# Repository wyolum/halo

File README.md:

# halo
Desktop Edge-lit portrait stand.

[Instructions:](https://wyolum.com/how-to-edge-lit-portrait-work-in-progress/)

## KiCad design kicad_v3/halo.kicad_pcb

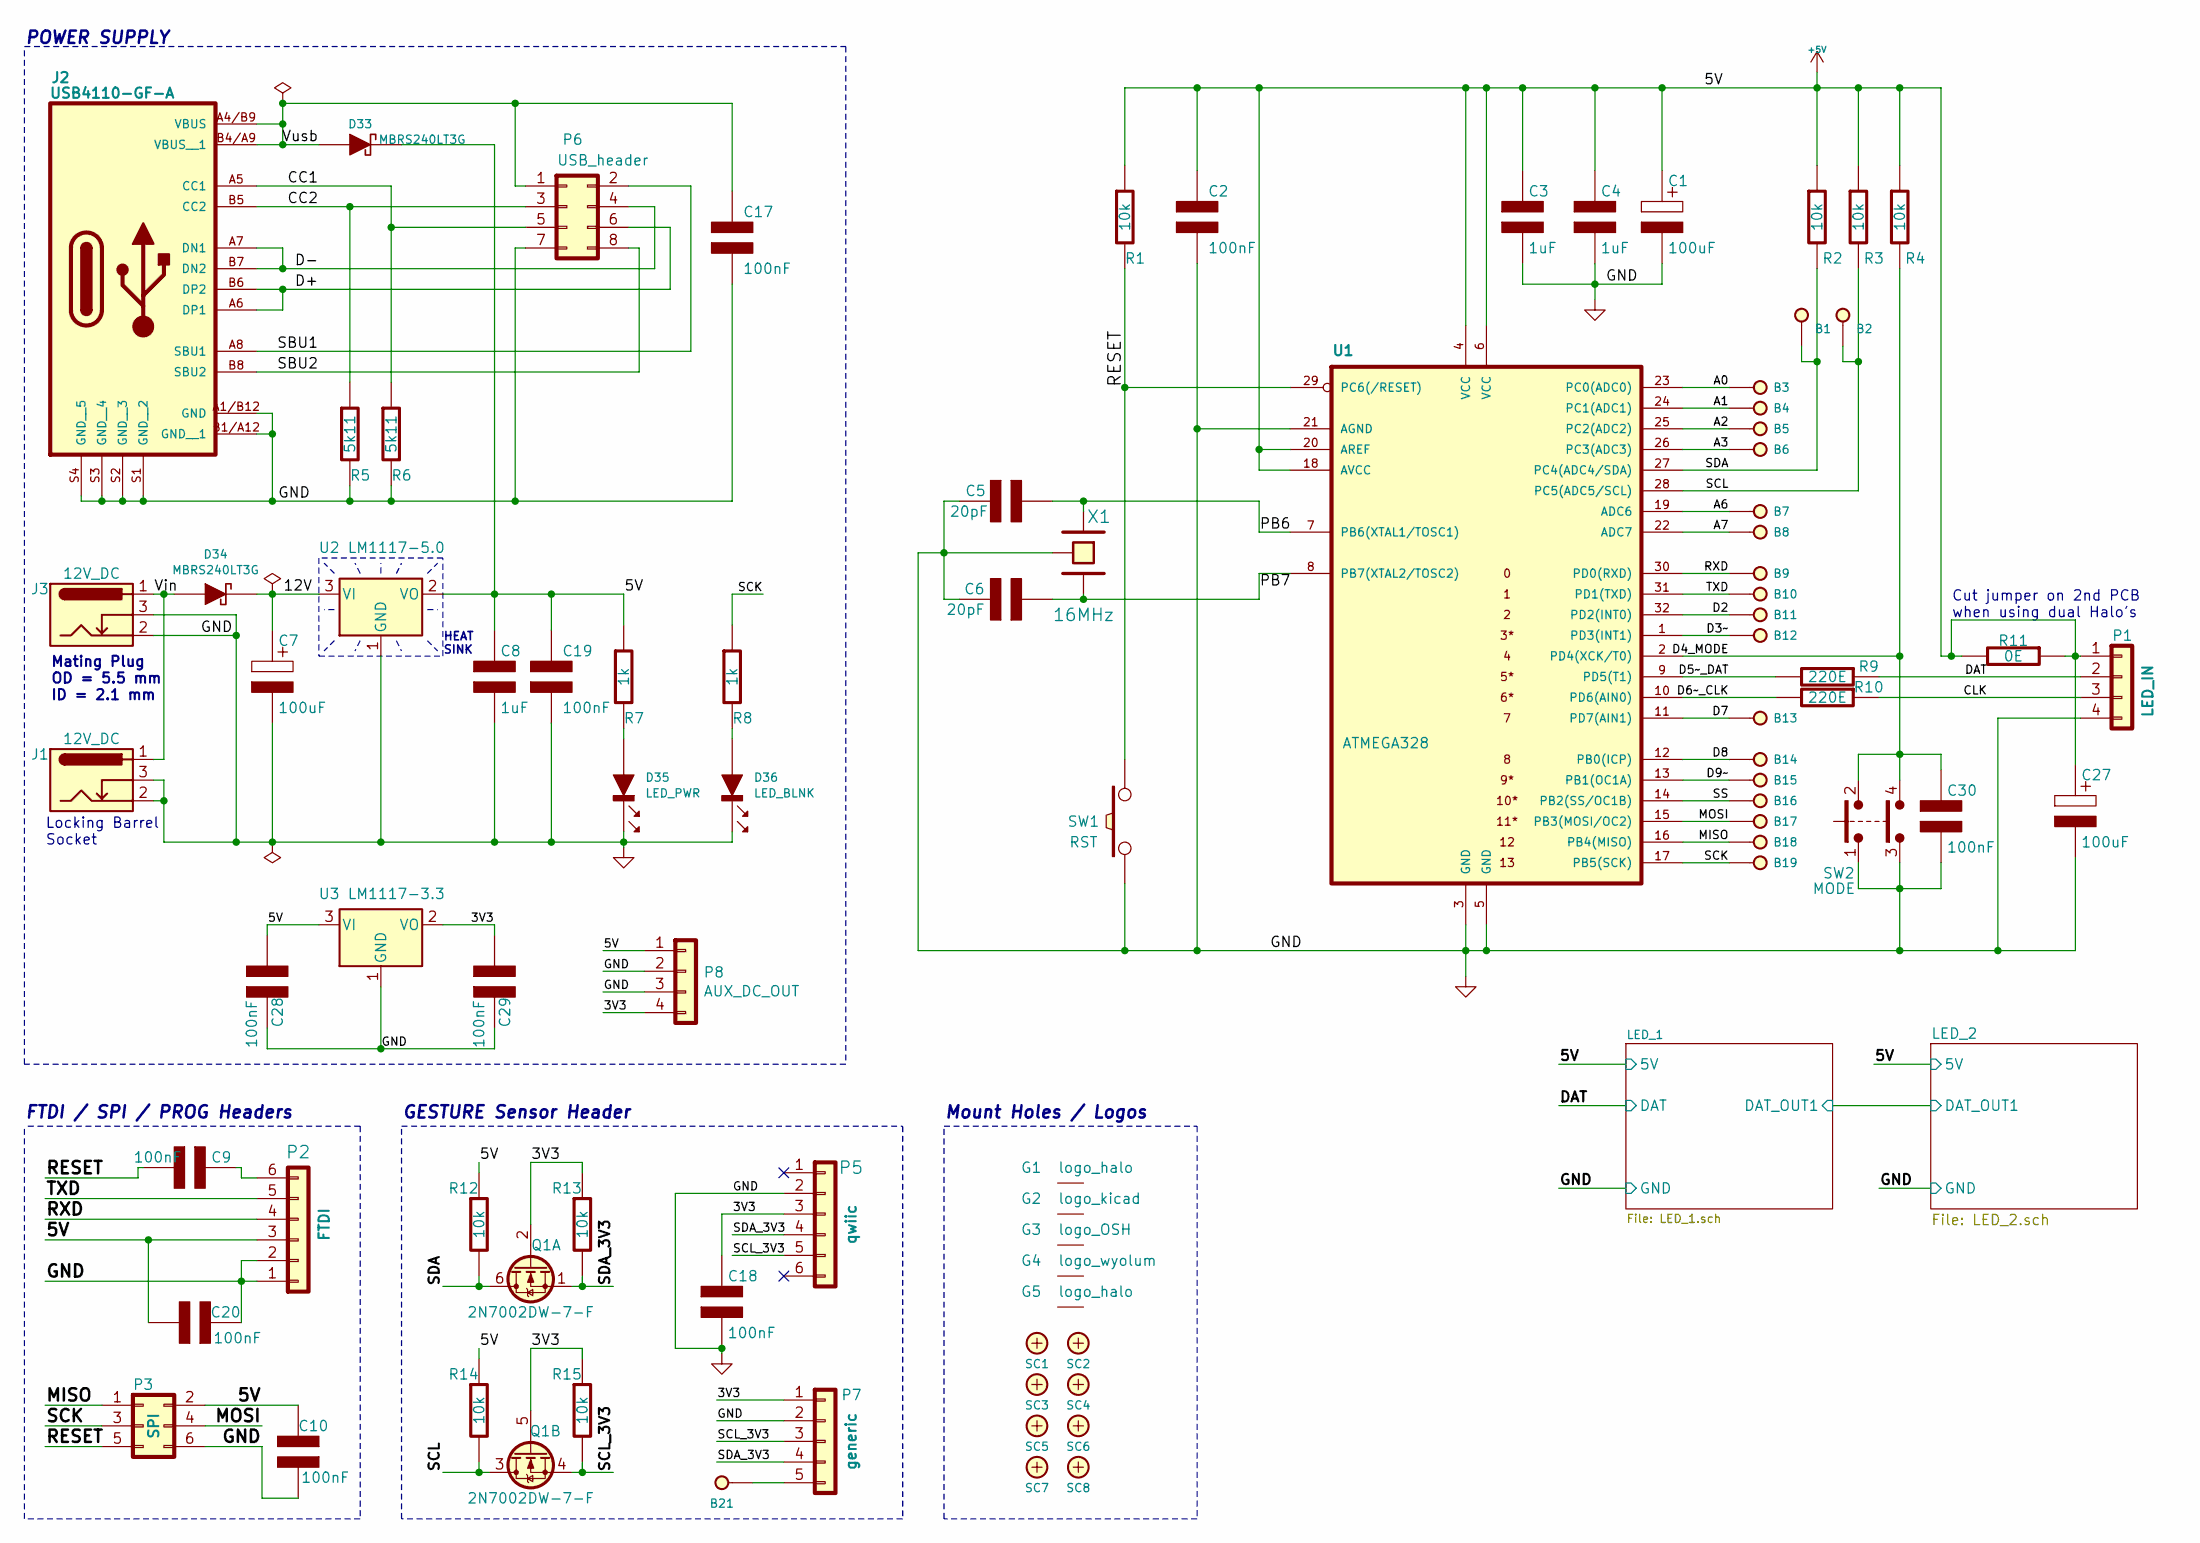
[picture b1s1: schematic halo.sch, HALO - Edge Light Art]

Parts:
B1, B2, B3, B4, B5, B6, B7, B8, B9, B10, B11, B12, B13, B14, B15, B16, B17, B18, B19, B21: I_O; breakout_smd
C1, C7, C27: 100uF; CP_Elec_6.3x7.7
C2, C9, C10, C17, C18, C19, C20, C28, C29, C30: 100nF; C_0805_2012Metric
C3, C4, C8: 1uF; C_0805_2012Metric
C5, C6: 20pF; C_0805_2012Metric; Digikey 490-1734-1-ND
D33, D34: MBRS240LT3G; D_SMB
D35: LED_PWR; LED_0805_2012Metric
D36: LED_BLNK; LED_0805_2012Metric
G1: logo_halo
G2: logo_kicad; logo_KiCad_12mm_SilkScreen
G3: logo_OSH; logo_OSHW_11.4x12mm_SilkScreen
G4: logo_wyolum
G5: logo_halo; logo_halo_10mm
J1: 12V_DC; conn_barrel
J2: USB4110-GF-A; GCT_USB4110-GF-A; PARTREV A
J3: 12V_DC; barrel_jack_DC-005-5A-2_5-SMT
P1: LED_IN; PinSocket_1x04_P2.54mm_Vertical_SMD_Pin1Left
P2: FTDI; PinHeader_1x06_P2.54mm_Vertical_SMD_Pin1Left
P3: SPI; TC2030-IDC
P5: qwiic; sparkfun_apds_9960_smd
P6: USB_header; PinHeader_2x04_P2.54mm_Vertical_SMD
P7: generic; generic_apds_9960_smd
P8: AUX_DC_OUT; PinSocket_1x04_P2.54mm_Vertical_SMD_Pin1Left
Q1: 2N7002DW-7-F; SOT-363_SC-70-6
R1, R2, R3, R4, R12, R13, R14, R15: 10k; R_0805_2012Metric
R5, R6: 5k11; R_0805_2012Metric
R7, R8: 1k; R_0805_2012Metric
R9, R10: 220E; R_0805_2012Metric
R11: 0E; R_0805_2012Metric
SC1, SC2, SC3, SC4, SC5, SC6, SC7, SC8: SCREW; MountingHole_3.2mm_M3_Pad_Via
SW1: RST; SW_Push_1P1T_NO_6x6mm_H9.5mm
SW2: MODE; PinHeader_2x02_P2.54mm_Vertical_SMD
U1: ATMEGA328; TQFP-32_7x7mm_P0.8mm
U2: LM1117-5.0; SOT-223-3_TabPin2
U3: LM1117-3.3; SOT-223-3_TabPin2
X1: 16MHz; Crystal_SMD_3225-4Pin_3.2x2.5mm

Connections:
+5V: C1.1, C2.1, C3.1, C4.1, C8.1, C10.2, C19.1, C20.1, C27.1, C28.1, D33.K, P1.1, P2.3, P3.2, P8.1, R1.1, R2.1, R3.1, R4.1, R7.1, R11.1, R11.2, R12.1, R14.1, U1.4 (VCC), U1.6 (VCC), U1.18 (AVCC), U1.20 (AREF), U2.2 (VO), U3.3 (VI); also elsewhere on the board
/3V3: C18.1, C29.1, P5.3, P7.1, P8.4, Q1.2 (G), Q1.5 (G), R13.1, R15.1, U3.2 (VO)
/12V: C7.1, D34.K, U2.3 (VI)
/A0: B3.1, U1.23 (PC0(ADC0))
/A1: B4.1, U1.24 (PC1(ADC1))
/A2: B5.1, U1.25 (PC2(ADC2))
/A3: B6.1, U1.26 (PC3(ADC3))
/A6: B7.1, U1.19 (ADC6)
/A7: B8.1, U1.22 (ADC7)
/CC1: J2.A5 (CC1), P6.5, R6.1
/CC2: J2.B5 (CC2), P6.3, R5.1
/CLK: P1.3, R10.1
/D2: B11.1, U1.32 (PD2(INT0))
/D3~~: B12.1, U1.1 (PD3(INT1))
/D4_MODE: C30.1, R4.2, SW2.2, SW2.4, U1.2 (PD4(XCK/T0))
/D5~~_DAT: R9.2, U1.9 (PD5(T1))
/D6~~_CLK: R10.2, U1.10 (PD6(AIN0))
/D7: B13.1, U1.11 (PD7(AIN1))
/D8: B14.1, U1.12 (PB0(ICP))
/D9~~: B15.1, U1.13 (PB1(OC1A))
/D+: J2.A6 (DP1), J2.B6 (DP2), P6.6
/D-: J2.A7 (DN1), J2.B7 (DN2), P6.4
/DAT: P1.2, R9.1; also elsewhere on the board
/MISO: B18.1, P3.1, U1.16 (PB4(MISO))
/MOSI: B17.1, P3.4, U1.15 (PB3(MOSI/OC2))
/PB6: C5.1, U1.7 (PB6(XTAL1/TOSC1)), X1.1
/PB7: C6.2, U1.8 (PB7(XTAL2/TOSC2)), X1.3
/RESET: C9.2, P3.5, R1.2, SW1.2, U1.29 (PC6(/RESET))
/RXD: B9.1, P2.4, U1.30 (PD0(RXD))
/SBU1: J2.A8 (SBU1), P6.2
/SBU2: J2.B8 (SBU2), P6.8
/SCK: B19.1, P3.3, R8.1, U1.17 (PB5(SCK))
/SCL: B2.1, Q1.3 (D), R3.2, R14.2, U1.28 (PC5(ADC5/SCL))
/SCL_3V3: P5.5, P7.3, Q1.4 (S), R15.2
/SDA: B1.1, Q1.6 (D), R2.2, R12.2, U1.27 (PC4(ADC4/SDA))
/SDA_3V3: P5.4, P7.4, Q1.1 (S), R13.2
/SS: B16.1, U1.14 (PB2(SS/OC1B))
/TXD: B10.1, P2.5, U1.31 (PD1(TXD))
/Vin: D34.A, J1.1, J3.1
/Vusb: C17.1, D33.A, J2.A4/B9 (VBUS), J2.B4/A9 (VBUS__1), P6.1
GND: C1.2, C2.2, C3.2, C4.2, C5.2, C6.1, C7.2, C8.2, C10.1, C17.2, C18.2, C19.2, C20.2, C27.2, C28.2, C29.2, C30.2, D35.K, D36.K, J1.2, J1.3, J2.A1/B12 (GND), J2.B1/A12 (GND__1), J2.S1 (GND__2), J2.S2 (GND__3), J2.S3 (GND__4), J2.S4 (GND__5), J3.2, J3.3, P1.4, P2.1, P2.2, P3.6, P5.2, P6.7, P7.2, P8.2, P8.3, R5.2, R6.2, SW1.1, SW2.1, SW2.3, U1.3 (GND), U1.5 (GND), U1.21 (AGND), U2.1 (GND), U3.1 (GND), X1.GND; also elsewhere on the board
unnamed: C9.1, P2.6
unnamed: D35.A, R7.2
unnamed: D36.A, R8.2

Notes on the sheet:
FTDI / SPI / PROG Headers
Mount Holes / Logos
HEAT SINK
Mating Plug OD = 5.5 mm ID = 2.1 mm
Cut jumper on 2nd PCB when using dual Halo's
Locking Barrel Socket
GESTURE Sensor Header
POWER SUPPLY

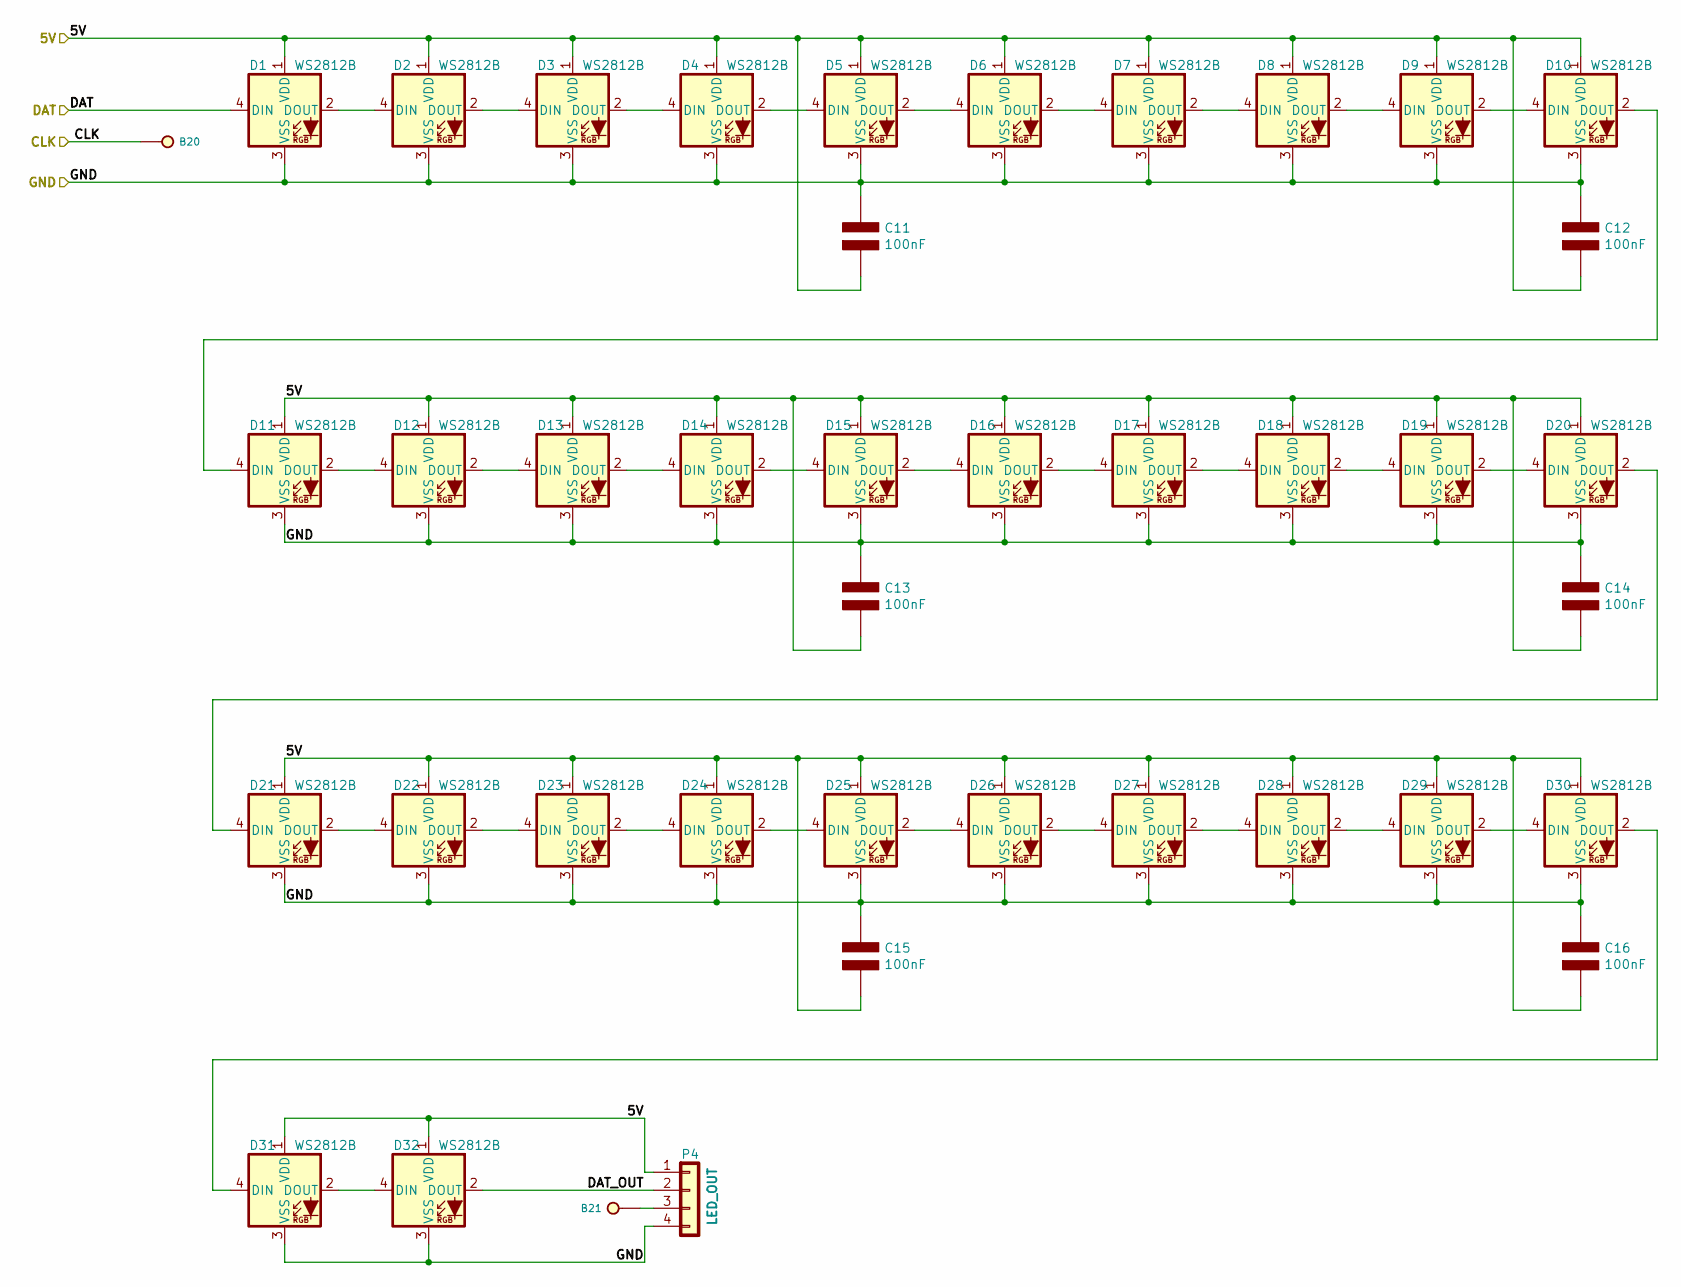
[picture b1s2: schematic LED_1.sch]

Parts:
B20, B21: I_O; breakout_smd
C11, C12, C13, C14, C15, C16: 100nF; C_0805_2012Metric
D1, D2, D3, D4, D5, D6, D7, D8, D9, D10, D11, D12, D13, D14, D15, D16, D17, D18, D19, D20, D21, D22, D23, D24, D25, D26, D27, D28, D29, D30, D31, D32: WS2812B; LED_WS2812B_PLCC4_5.0x5.0mm_P3.2mm
P4: LED_OUT; PinSocket_1x04_P2.54mm_Vertical_SMD_Pin1Left

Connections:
+5V: C11.2, C12.2, C13.2, C14.2, C15.2, C16.2, D1.1 (VDD), D2.1 (VDD), D3.1 (VDD), D4.1 (VDD), D5.1 (VDD), D6.1 (VDD), D7.1 (VDD), D8.1 (VDD), D9.1 (VDD), D10.1 (VDD), D11.1 (VDD), D12.1 (VDD), D13.1 (VDD), D14.1 (VDD), D15.1 (VDD), D16.1 (VDD), D17.1 (VDD), D18.1 (VDD), D19.1 (VDD), D20.1 (VDD), D21.1 (VDD), D22.1 (VDD), D23.1 (VDD), D24.1 (VDD), D25.1 (VDD), D26.1 (VDD), D27.1 (VDD), D28.1 (VDD), D29.1 (VDD), D30.1 (VDD), D31.1 (VDD), D32.1 (VDD), P4.1; also elsewhere on the board
/DAT: D1.4 (DIN); also elsewhere on the board
GND: C11.1, C12.1, C13.1, C14.1, C15.1, C16.1, D1.3 (VSS), D2.3 (VSS), D3.3 (VSS), D4.3 (VSS), D5.3 (VSS), D6.3 (VSS), D7.3 (VSS), D8.3 (VSS), D9.3 (VSS), D10.3 (VSS), D11.3 (VSS), D12.3 (VSS), D13.3 (VSS), D14.3 (VSS), D15.3 (VSS), D16.3 (VSS), D17.3 (VSS), D18.3 (VSS), D19.3 (VSS), D20.3 (VSS), D21.3 (VSS), D22.3 (VSS), D23.3 (VSS), D24.3 (VSS), D25.3 (VSS), D26.3 (VSS), D27.3 (VSS), D28.3 (VSS), D29.3 (VSS), D30.3 (VSS), D31.3 (VSS), D32.3 (VSS), P4.4; also elsewhere on the board
unnamed: D1.2 (DOUT), D2.4 (DIN)
unnamed: D2.2 (DOUT), D3.4 (DIN)
unnamed: D3.2 (DOUT), D4.4 (DIN)
unnamed: D4.2 (DOUT), D5.4 (DIN)
unnamed: D5.2 (DOUT), D6.4 (DIN)
unnamed: D6.2 (DOUT), D7.4 (DIN)
unnamed: D7.2 (DOUT), D8.4 (DIN)
unnamed: D8.2 (DOUT), D9.4 (DIN)
unnamed: D10.2 (DOUT), D11.4 (DIN)
unnamed: D9.2 (DOUT), D10.4 (DIN)
unnamed: D11.2 (DOUT), D12.4 (DIN)
unnamed: D12.2 (DOUT), D13.4 (DIN)
unnamed: D13.2 (DOUT), D14.4 (DIN)
unnamed: D14.2 (DOUT), D15.4 (DIN)
unnamed: D15.2 (DOUT), D16.4 (DIN)
unnamed: D16.2 (DOUT), D17.4 (DIN)
unnamed: D17.2 (DOUT), D18.4 (DIN)
unnamed: D18.2 (DOUT), D19.4 (DIN)
unnamed: D19.2 (DOUT), D20.4 (DIN)
unnamed: D20.2 (DOUT), D21.4 (DIN)
unnamed: D21.2 (DOUT), D22.4 (DIN)
unnamed: D22.2 (DOUT), D23.4 (DIN)
unnamed: D23.2 (DOUT), D24.4 (DIN)
unnamed: D24.2 (DOUT), D25.4 (DIN)
unnamed: D25.2 (DOUT), D26.4 (DIN)
unnamed: D26.2 (DOUT), D27.4 (DIN)
unnamed: D27.2 (DOUT), D28.4 (DIN)
unnamed: D28.2 (DOUT), D29.4 (DIN)
unnamed: D29.2 (DOUT), D30.4 (DIN)
unnamed: D30.2 (DOUT), D31.4 (DIN)
unnamed: D31.2 (DOUT), D32.4 (DIN)

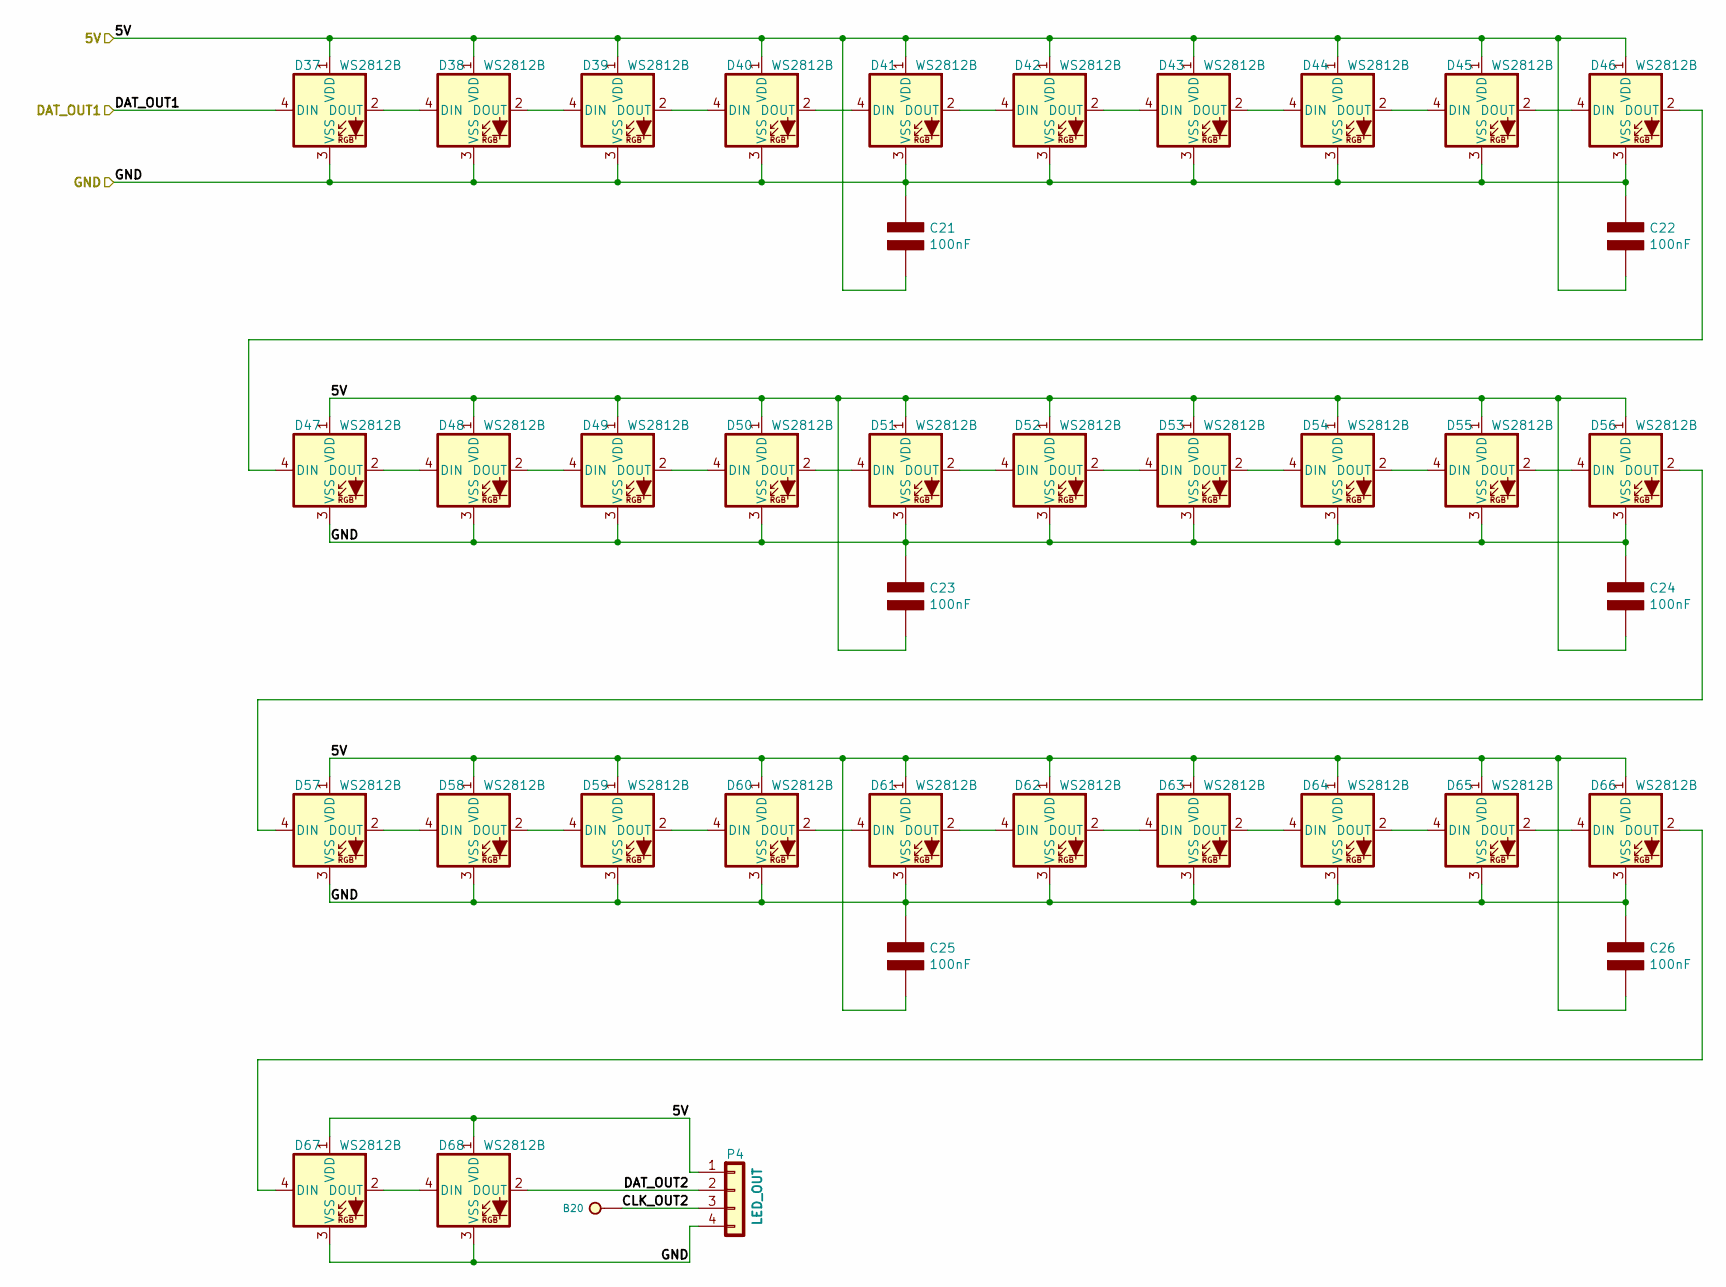
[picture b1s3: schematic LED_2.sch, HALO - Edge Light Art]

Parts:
B20: I_O; breakout_smd
C21, C22, C23, C24, C25, C26: 100nF; C_0805_2012Metric
D37, D38, D39, D40, D41, D42, D43, D44, D45, D46, D47, D48, D49, D50, D51, D52, D53, D54, D55, D56, D57, D58, D59, D60, D61, D62, D63, D64, D65, D66, D67, D68: WS2812B; LED_WS2812B_PLCC4_5.0x5.0mm_P3.2mm
P4: LED_OUT; PinSocket_1x04_P2.54mm_Vertical_SMD_Pin1Left

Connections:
+5V: C21.2, C22.2, C23.2, C24.2, C25.2, C26.2, D37.1 (VDD), D38.1 (VDD), D39.1 (VDD), D40.1 (VDD), D41.1 (VDD), D42.1 (VDD), D43.1 (VDD), D44.1 (VDD), D45.1 (VDD), D46.1 (VDD), D47.1 (VDD), D48.1 (VDD), D49.1 (VDD), D50.1 (VDD), D51.1 (VDD), D52.1 (VDD), D53.1 (VDD), D54.1 (VDD), D55.1 (VDD), D56.1 (VDD), D57.1 (VDD), D58.1 (VDD), D59.1 (VDD), D60.1 (VDD), D61.1 (VDD), D62.1 (VDD), D63.1 (VDD), D64.1 (VDD), D65.1 (VDD), D66.1 (VDD), D67.1 (VDD), D68.1 (VDD), P4.1; also elsewhere on the board
GND: C21.1, C22.1, C23.1, C24.1, C25.1, C26.1, D37.3 (VSS), D38.3 (VSS), D39.3 (VSS), D40.3 (VSS), D41.3 (VSS), D42.3 (VSS), D43.3 (VSS), D44.3 (VSS), D45.3 (VSS), D46.3 (VSS), D47.3 (VSS), D48.3 (VSS), D49.3 (VSS), D50.3 (VSS), D51.3 (VSS), D52.3 (VSS), D53.3 (VSS), D54.3 (VSS), D55.3 (VSS), D56.3 (VSS), D57.3 (VSS), D58.3 (VSS), D59.3 (VSS), D60.3 (VSS), D61.3 (VSS), D62.3 (VSS), D63.3 (VSS), D64.3 (VSS), D65.3 (VSS), D66.3 (VSS), D67.3 (VSS), D68.3 (VSS), P4.4; also elsewhere on the board
unnamed: D37.2 (DOUT), D38.4 (DIN)
unnamed: D38.2 (DOUT), D39.4 (DIN)
unnamed: D39.2 (DOUT), D40.4 (DIN)
unnamed: D40.2 (DOUT), D41.4 (DIN)
unnamed: D41.2 (DOUT), D42.4 (DIN)
unnamed: D42.2 (DOUT), D43.4 (DIN)
unnamed: D43.2 (DOUT), D44.4 (DIN)
unnamed: D44.2 (DOUT), D45.4 (DIN)
unnamed: D45.2 (DOUT), D46.4 (DIN)
unnamed: D46.2 (DOUT), D47.4 (DIN)
unnamed: D47.2 (DOUT), D48.4 (DIN)
unnamed: D48.2 (DOUT), D49.4 (DIN)
unnamed: D49.2 (DOUT), D50.4 (DIN)
unnamed: D50.2 (DOUT), D51.4 (DIN)
unnamed: D51.2 (DOUT), D52.4 (DIN)
unnamed: D52.2 (DOUT), D53.4 (DIN)
unnamed: D53.2 (DOUT), D54.4 (DIN)
unnamed: D54.2 (DOUT), D55.4 (DIN)
unnamed: D55.2 (DOUT), D56.4 (DIN)
unnamed: D56.2 (DOUT), D57.4 (DIN)
unnamed: D57.2 (DOUT), D58.4 (DIN)
unnamed: D58.2 (DOUT), D59.4 (DIN)
unnamed: D59.2 (DOUT), D60.4 (DIN)
unnamed: D60.2 (DOUT), D61.4 (DIN)
unnamed: D61.2 (DOUT), D62.4 (DIN)
unnamed: D62.2 (DOUT), D63.4 (DIN)
unnamed: D63.2 (DOUT), D64.4 (DIN)
unnamed: D64.2 (DOUT), D65.4 (DIN)
unnamed: D65.2 (DOUT), D66.4 (DIN)
unnamed: D66.2 (DOUT), D67.4 (DIN)
unnamed: D67.2 (DOUT), D68.4 (DIN)

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
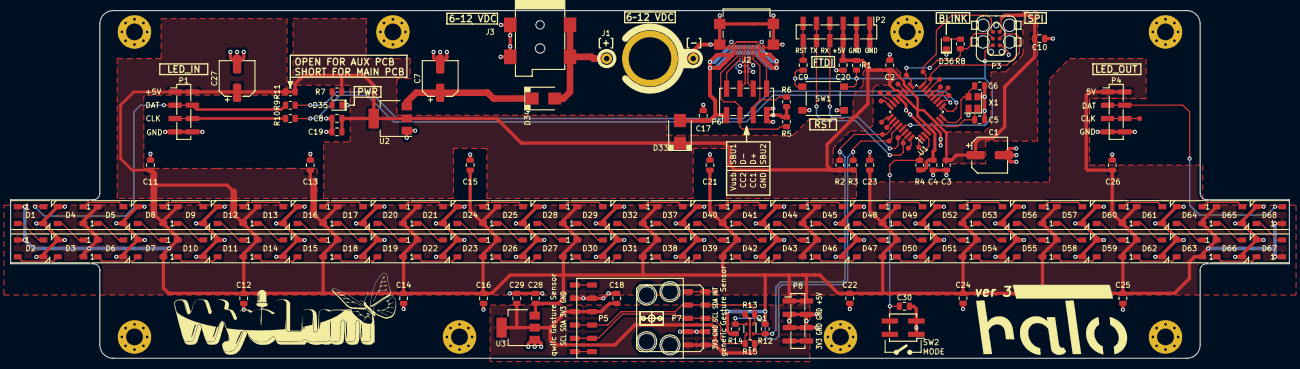
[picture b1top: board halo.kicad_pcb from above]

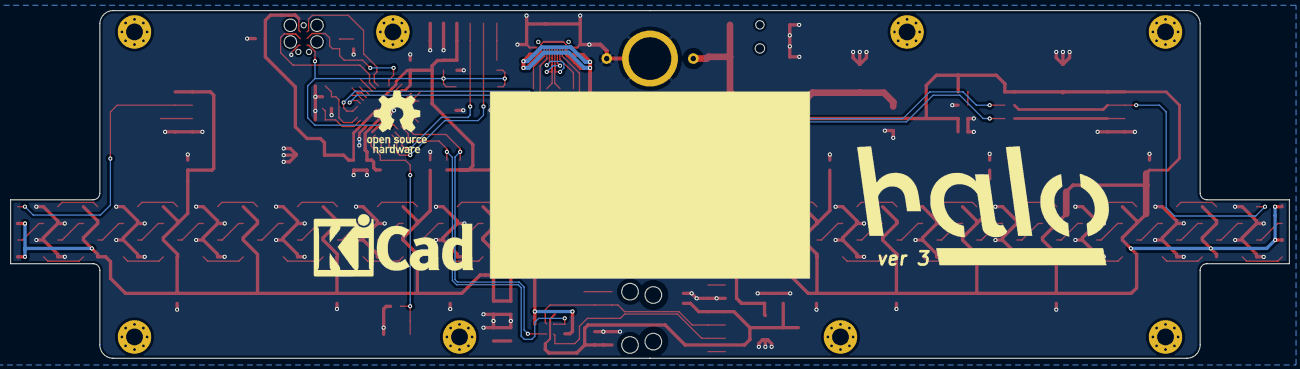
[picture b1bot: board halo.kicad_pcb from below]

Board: 2 copper layers, 243.8 x 66.3 mm, 165 parts (3 on the bottom side), 110 nets.

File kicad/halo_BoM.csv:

"Id";"Designator";"Package";"Quantity";"Designation";"Supplier and ref";
1;"C18,C10,C9,C11,C12,C13,C14,C15,C16,C2,C17,C19,C20";"C_0805_2012Metric";13;"100nF";;;
2;"P6";"PinHeader_2x04_P2.54mm_Vertical_SMD";1;"USB_header";;;
3;"J2";"GCT_USB4110-GF-A";1;"USB4110-GF-A";;;
4;"C1,C7";"CP_Elec_4x5.8";2;"22uF";;;
5;"SW1";"SW_Push_1P1T_NO_6x6mm_H9.5mm";1;"RST";;;
6;"U2";"SOT-223-3_TabPin2";1;"LM1117-5.0";;;
7;"C6,C5";"C_0805_2012Metric";2;"20pF";;;
8;"J3";"barrel_jack_DC-005-5A-2_5-SMT";1;"12V_DC";;;
9;"D32,D31,D1,D2,D3,D4,D5,D6,D7,D8,D9,D10,D11,D12,D13,D14,D15,D16,D17,D18,D19,D20,D21,D22,D23,D24,D25,D26,D27,D28,D29,D30";"LED_WS2812B_PLCC4_5.0x5.0mm_P3.2mm";32;"WS2812B";;;
10;"R1,R2,R3,R4";"R_0805_2012Metric";4;"10k";;;
11;"B1,B2,B3,B4,B5,B6,B7,B8,B9,B10,B11,B12,B13,B14,B15,B16,B17,B18,B19,B20,B21";"breakout_smd";21;"I_O";;;
12;"C3,C4,C8";"C_0805_2012Metric";3;"1uF";;;
13;"D35";"LED_0805_2012Metric";1;"LED_PWR";;;
14;"D36";"LED_0805_2012Metric";1;"LED_BLNK";;;
15;"P1";"PinSocket_1x04_P2.54mm_Vertical_SMD_Pin1Left";1;"LED_IN";;;
16;"P2";"PinHeader_1x06_P2.54mm_Vertical_SMD_Pin1Left";1;"FTDI";;;
17;"P3";"PinHeader_2x03_P2.54mm_Vertical_SMD";1;"SPI";;;
18;"P4";"PinSocket_1x04_P2.54mm_Vertical_SMD_Pin1Left";1;"LED_OUT";;;
19;"R5,R6";"R_0805_2012Metric";2;"5k11";;;
20;"R7,R8";"R_0805_2012Metric";2;"1k";;;
21;"SC1,SC2,SC3,SC4,SC5,SC6,SC7,SC8";"MountingHole_3.2mm_M3_Pad_Via";8;"SCREW";;;
22;"U1";"TQFP-32_7x7mm_P0.8mm";1;"ATMEGA328";;;
23;"X1";"Crystal_SMD_3225-4Pin_3.2x2.5mm";1;"16MHz";;;
24;"G1";"logo_halo";1;"logo_halo";;;
25;"G4";"logo_wyolum";1;"logo_wyolum";;;
26;"G2";"logo_KiCad_12mm_SilkScreen";1;"logo_kicad";;;
27;"G3";"logo_OSHW_11.4x12mm_SilkScreen";1;"logo_OSH";;;
28;"SW2";"PinHeader_2x02_P2.54mm_Vertical_SMD";1;"MODE";;;
29;"D33,D34";"D_SMB";2;"MBRS240LT3G";;;
30;"P5";"sparkfun_apds_9960_smd";1;"qwiic";;;
31;"R9,R10";"R_0805_2012Metric";2;"0E";;;

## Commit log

2020-10-25 reorg
2020-10-28 added 3D FreeCAD case
2020-10-31 added kicad schematic
2020-10-31 added kicad PCB wip
2020-10-31 added qwiic I2C conn for ToF sensor
2020-11-01 added PCB review needed
2020-11-03 Gerber BoM ready
2020-11-05 Gerber BoM Position files for JLCpcb
2020-11-24 added gesture sensor
2020-11-24 added libs
2020-11-28 add pcb trace
2020-11-30 added gesture sensor standoff
2020-12-10 halo_v2 WIP
2020-12-13 halo_v2 almost done
2020-12-13 halo_v2 removed the large STEP file
2020-12-13 halo_v2 JLCpcb files ready
2020-12-13 halo_v2 added enclosure laser and 3DP files
2020-12-17 halo_v2 modified 3D print corners
2020-12-23 add example Halov2 program
2020-12-25 halo_v3 added renders
2020-12-30 add whole case laser cutting file for V2
2020-12-30 update sparkfun gesture library to support generic boards
2020-12-30 remove older sparkfun library
2021-01-05 Halov2.1 demo separate front and back addressability
2021-01-09 add gesture hole and ftdi opening
2021-01-10 halo_v3 added clock face SVG's
2021-01-16 add powertest
2021-01-24 halo_v3 added springy wedge corner pieces
2021-02-07 added clock face pdf
2021-02-07 added clock code
2021-04-18 added setter that sets RTC from compile time
2021-04-18 added compile time setting to Clock.ino
2021-08-10 Added Halov2.1 that inlcludes two rows of leds
2022-10-02 added files for 'NOT A MAP'
2023-08-06 added Halo v2 render images folders
